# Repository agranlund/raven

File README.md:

# Raven
### A homemade computer based on Motorola MC68060 + DSP56303
This computer is designed to be an Atari compatible clone. It runs clean GEM/TOS applications natively, and very old hardware-banging ST games through an emulation layer.

Some of the more imporant bits in this slightly disorganized repo:
- [Hardware](hw/raven/a2/) - KiCad schematics and PCB. Interactive BOM, revision history.
- [Firmware](fw/) - [CUPL bus logic](fw/a2/), [CKBD keyboard controller](fw/ckbd/)
- [Software](sw/) - [bootloader and monitor](sw/rom/boot/), [TOS bios extension](sw/rvbios/), [ISA PnP bios and drivers](sw/isa/), [graphics drivers](sw/rvnova/), [sound drivers](sw/rvsnd/), [misc utils](sw/tools/)

## Links and resources:
- Youtube: https://www.youtube.com/@granlund23/videos
- Forum: https://www.exxosforum.co.uk/forum/viewforum.php?f=119

## This is not a consumer product.
I have no formal EE training or education. The computer is primarily designed as a one-off for myself, for fun and learning and as a platform that can provide a whole range of interesting areas of programming and/or hardware tinkering.

All hardware and software sources are provided as-is and for free but comes with no guarantees or promise of support.

The computer works for me and can run EmuTOS, FreeMiNT or MagiC but if you decide to build or buy this board I very much recommend coming in with a DIY mindset -- Knowledge and tools to perform hardware-level debugging and/or very low level software debugging is highly recommended.

The forum is also a good place to get help and ask questions regarding bringup or any other topics.

Rev.A1 is slightly easier to build and has seen 10+ other people building working ones.

Rev.A2 is an incremental update where the largest addition is the DSP56303 but it has only been built and tested by myself so far.

## Specifications Rev.A2
- Motorola 68060 CPU @ 96Mhz
- Motorola 56303 DSP @ 90Mhz
- Max 48MB RAM
- Max 16MB ROM
- USB Mouse & Keyboard
- 1Mbps serial port
- Legacy Atari serial port
- Legacy Atari parallel port
- Legacy Atari joystick ports
- IDE Harddisk interface
- Realtime clock
- Midi In/Out
- YM2149 sound
- MC68901 MFP x2
- ISA 16bit expansion slots x4

## Required or recommended parts
- Raven motherboard
	- [Revision.A2](hw/raven/a2/)
    - [Revision.A1](hw/raven/a1/)
    	- [USB upgrade](hw/raven/a1/upgrades/ckbd/)
- RAM modules
    - [16MB 55ns](hw/simm/ram_16M55/)
- ROM module
    - [55ns SMD](hw/simm/rom_SMD/)
    - [55ns PLCC](hw/simm/rom_PLCC/)
- ATX power supply
- USB keyboard and mouse (PS/2 for Rev.A1 without USB upgrade)
- Some kind of suitable 44pin IDE->CF adapter
- RS232<->USB cable capable of 1Mbps
- ISA graphics card.
    - SVGA with hardware acceleration
        - Cirrus GD5434, GD5429, GD5428, GD5426
        - WDC WD90C33, WD90C31
        - Tseng ET4000/W32i
        - ATI Mach32
    - SVGA without hardware acceleration
        - Tseng ET4000AX
        - (untested) Cirrus GD5424, GD5422
        - (untested) WD90C30
    - Cards not listed above have a high chance of working but only in standard VGA resolutions.
- ISA Network card.
	- RTL8019AS based card
- ISA soundcard
	- SoundBlaster compatible
	- Gravis Ultrasound

## Additional tools
- [ROM Simm programmer](hw/simm/programmer/)
- Programmer for ATF1508AS, for example ATDH1150-USB
- Programmer for ATF22V10C, for example XGecu TL866II-Plus
- (Rev.A1 without USB upgrade) Programmer for PIC16F876A, for example XGecu TL866II-Plus

## License

Hardware + CUPL logic are CERN-OHL-2.0. My own software is mostly GPL v2+, 3rd party code keeps its original license. Where a folder differs it'll have its own license file.

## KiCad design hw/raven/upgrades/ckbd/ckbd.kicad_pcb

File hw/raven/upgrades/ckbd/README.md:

# Eiffel upgrade module (rev.d) for Raven.A1

- Plugs into the Eiffel socket instead of the Eiffel PIC.
- Retains support for PS/2 mouse+keyboard, joystick and motherboard temperature sensor.
- Adds USB mouse and keyboard support on an internal USB header.
- Adds support for legacy Atari and Amiga mice (*)
- Adds support for reading CPU temperature (*)
- Adds support for software controlled shutdown (*)

### Firmware:
Binary, sourcecode, and programming instructions can be found here:
* [ckbd firmware](../../../../fw/ckbd/) 

(*) Features marked with an asterix requires soldering patch wires on the motherboard.
All solder points are available on through hole components and can be done on the underside of the motherboard.

#### Support for right mouse button on Legacy mice (not needed for USB or PS2)
- J606:A9  <-> J606:B6 (mouse right button - joystick1 fire button)
#### Support for CPU temperature readout
- U107:M15 <-> U107:M16 (CPU Therm1 - GND)
- U107:L15 <-> U301:26 (CPU Therm0 - Eiffel:Temp2)
#### Support for software controlled shutdown
- SW201:2 <-> U301:25 (PWR switch - Eiffel:PwrOff)

## BOM

| Manufacturer  | Part number       | Value     | Qty | Ref                 | Note |
|---------------|-------------------|-----------|-----|---------------------|------|
| WCH           | CH559L            | CH559L    | 1   | U101                |      |
| Yageo         | RT1206FRE0710KL   | 10K       | 3   | R103,R105,R106      |      |
| Yageo         | RT1206FRE071KL    | 1K        | 4   | R101,R102,R104,R107 |      |
| Kemet         | C1206C105K4RACTU  | 1u        | 2   | C103,C104           |      |
| Kemet         | C1206C104K5RACTU  | 0.1u      | 2   | C102,C105           |      |
| Kemet         | C1206C334K5RACTU  | 0.33u     | 1   | C101                |      |
| ?             | pinheader round   | 1x14      | 2   | J101,J102           | (1)  |
| ?             | pinheader square  | 2x5       | 1   | J103                | (2)  |
| ?             | pinheader square  | 1x4       | 1   | J104                | (2)  |

(1) J101,J102 needs to be round machined pins that can fit in a dip socket.
40-pin breakaway strips can be found here:
https://www.exxosforum.co.uk/atari/store2/#0132

(2) J103,J104 are standard square pin headers which can be found anywhere.
40-pin breakaway strips can be found here:
https://www.exxosforum.co.uk/atari/store2/#0158

## Notes for previous rev.c boards:

The eiffel controlled fan does not work in the previous version of this board.

This can be fixed by soldering a ~1K resistor connecting pins FAN1 and +5V which are both found on the right row of the Eiffel connector.

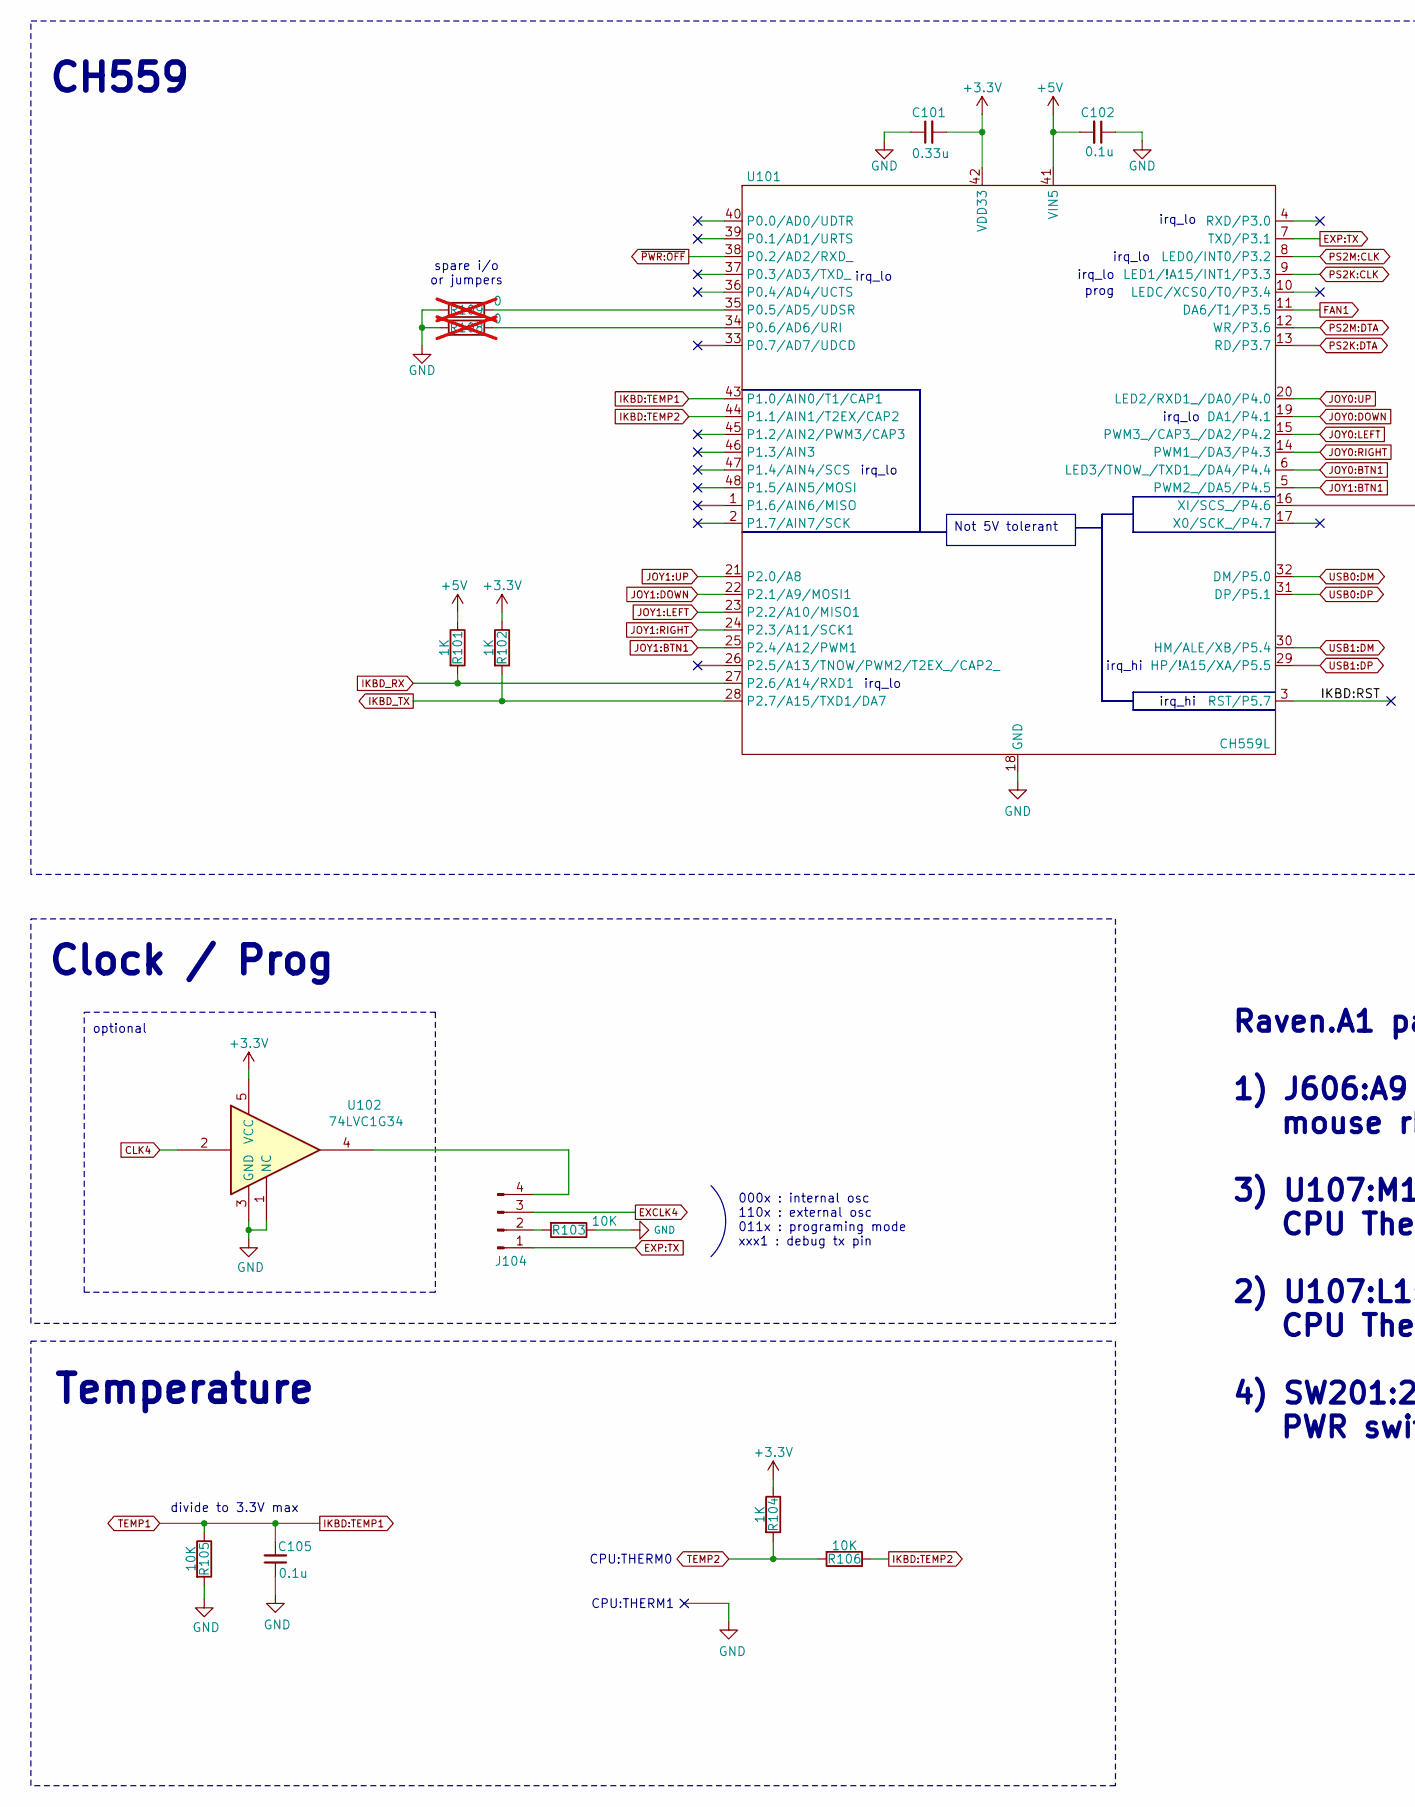
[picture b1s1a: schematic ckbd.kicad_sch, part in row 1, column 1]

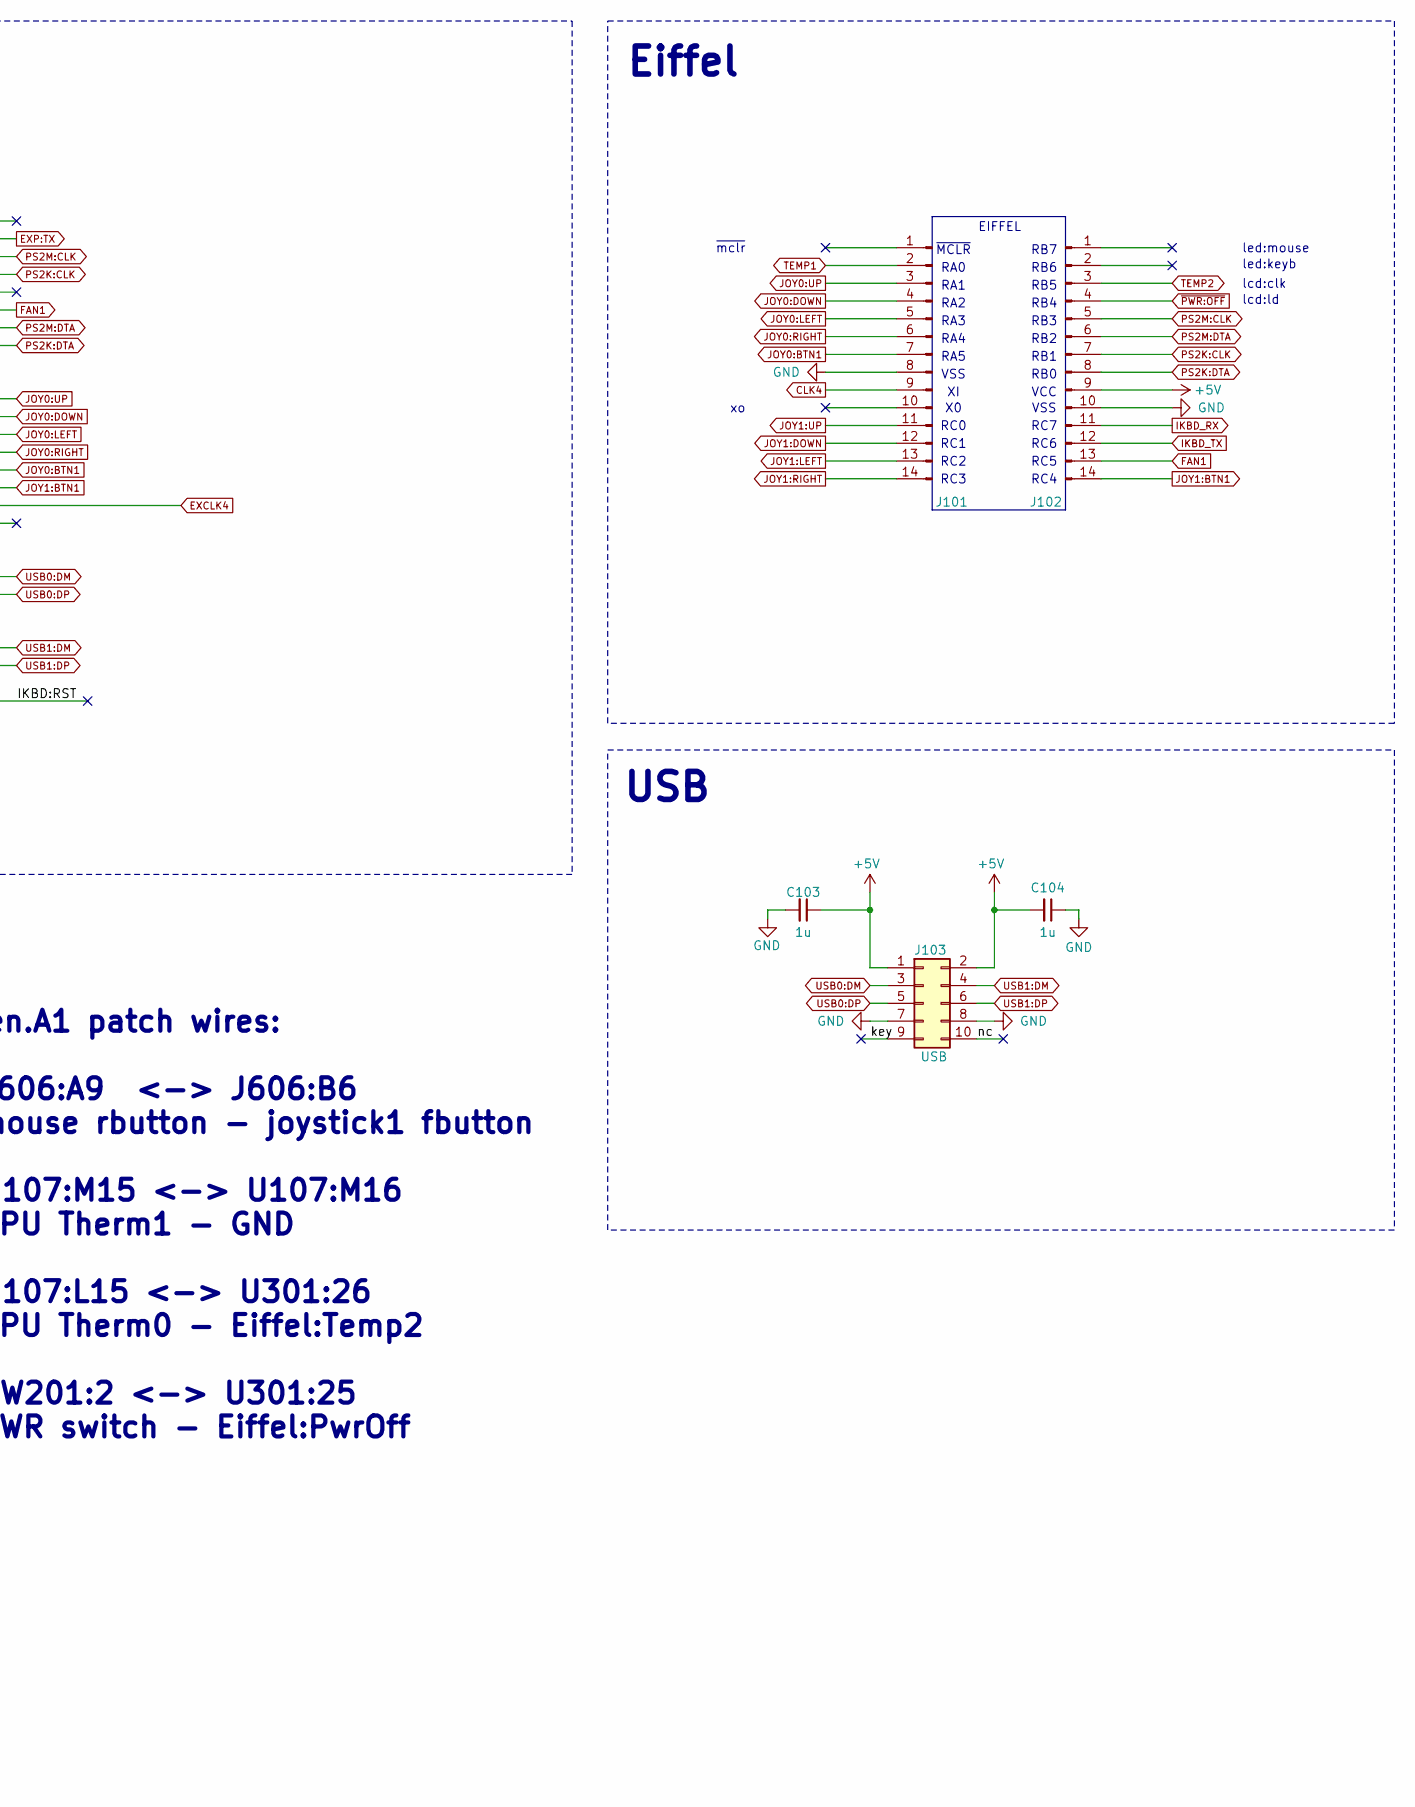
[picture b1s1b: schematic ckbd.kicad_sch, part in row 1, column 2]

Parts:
C101: 0.33u; C_1206_3216Metric_Pad1.33x1.80mm_HandSolder; Manufacturer_Part_Number C1206C334K5RACTU
C102, C105: 0.1u; C_1206_3216Metric_Pad1.33x1.80mm_HandSolder; Manufacturer_Part_Number C1206C104K5RACTU
C103, C104: 1u; C_1206_3216Metric_Pad1.33x1.80mm_HandSolder; Manufacturer_Part_Number C1206C105K4RACTU
J101, J102: PinHeader_1x14_P2.54mm_Vertical
J103: USB; PinHeader_2x05_P2.54mm_Vertical
J104: PinHeader_1x04_P2.54mm_Vertical; Manufacturer_Part_Number 61300411121
R101, R102, R104: 1K; R_1206_3216Metric_Pad1.30x1.75mm_HandSolder; Manufacturer_Part_Number RT1206FRE071KL
R103, R105, R106: 10K; R_1206_3216Metric_Pad1.30x1.75mm_HandSolder; Manufacturer_Part_Number RT1206FRE0710KL
R108, R109: 0; R_1206_3216Metric; not fitted
U101: CH559L; LQFP-48_7x7mm_P0.5mm; Manufacturer_Part_Number CH559L
U102: 74LVC1G34; SOT-23-5_HandSoldering; Manufacturer_Part_Number SN74LVC1G34DBVRG4

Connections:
+3.3V: C101.2, R102.1, R104.1, U101.42 (VDD33), U102.5 (VCC)
+5V: C102.2, C103.1, C104.2, J102.9, J103.1, J103.2, R101.1, U101.41 (VIN5); also elsewhere on the board
/IKBD:RST: U101.3 (RST/P5.7)
/nc: J103.10
CLK4: J101.9, U102.2
EXCLK4: J104.3, U101.16 (XI/SCS_/P4.6)
EXP:TX: J104.1, U101.7 (TXD/P3.1)
FAN1: J102.13, U101.11 (DA6/T1/P3.5); also elsewhere on the board
GND: C101.1, C102.1, C103.2, C104.1, C105.1, J101.8, J102.10, J103.7, J103.8, R103.1, R105.2, R108.1, R109.1, U101.18 (GND), U102.1 (NC), U102.3 (GND)
IKBD:TEMP1: C105.2, J101.2, R105.1, U101.43 (P1.0/AIN0/T1/CAP1)
IKBD:TEMP2: R106.1, U101.44 (P1.1/AIN1/T2EX/CAP2)
IKBD_RX: J102.11, R101.2, U101.27 (P2.6/A14/RXD1)
IKBD_TX: J102.12, R102.2, U101.28 (P2.7/A15/TXD1/DA7)
JOY0:BTN1: J101.7, U101.6 (LED3/TNOW_/TXD1_/DA4/P4.4)
JOY0:DOWN: J101.4, U101.19 (DA1/P4.1)
JOY0:LEFT: J101.5, U101.15 (PWM3_/CAP3_/DA2/P4.2)
JOY0:RIGHT: J101.6, U101.14 (PWM1_/DA3/P4.3)
JOY0:UP: J101.3, U101.20 (LED2/RXD1_/DA0/P4.0)
JOY1:BTN1: J102.14, U101.5 (PWM2_/DA5/P4.5), U101.25 (P2.4/A12/PWM1)
JOY1:DOWN: J101.12, U101.22 (P2.1/A9/MOSI1)
JOY1:LEFT: J101.13, U101.23 (P2.2/A10/MISO1)
JOY1:RIGHT: J101.14, U101.24 (P2.3/A11/SCK1)
JOY1:UP: J101.11, U101.21 (P2.0/A8)
unnamed: J104.2, R103.2
unnamed: J104.4, U102.4
unnamed: R109.2, U101.35 (P0.5/AD5/UDSR)
unnamed: R108.2, U101.34 (P0.6/AD6/URI)
PS2K:CLK: J102.7, U101.9 (LED1/!A15/INT1/P3.3)
PS2K:DTA: J102.8, U101.13 (RD/P3.7)
PS2M:CLK: J102.5, U101.8 (LED0/INT0/P3.2)
PS2M:DTA: J102.6, U101.12 (WR/P3.6)
TEMP2: J102.3, R104.2, R106.2
USB0:DM: J103.3, U101.32 (DM/P5.0)
USB0:DP: J103.5, U101.31 (DP/P5.1)
USB1:DM: J103.4, U101.30 (HM/ALE/XB/P5.4)
USB1:DP: J103.6, U101.29 (HP/!A15/XA/P5.5)
~PWR:OFF: J102.4, U101.38 (P0.2/AD2/RXD_)

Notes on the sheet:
RC7
EIFFEL
RB6
RC4
irq_lo
RA4
RA0
VCC
RB2
RB5
RB7
RC0
RB1
Eiffel
irq_hi
~{MCLR}
led:keyb
lcd:clk
CH559
USB
RB4
lcd:ld
RC3
000x : internal osc 110x : external osc 011x : programing mode xxx1 : debug tx pin
CPU:THERM1
divide to 3.3V max
RB0
RC6
Temperature
CPU:THERM0
RA3
RA2
prog
VSS
led:mouse
RB3
RC2
Clock / Prog
RA5
RA1

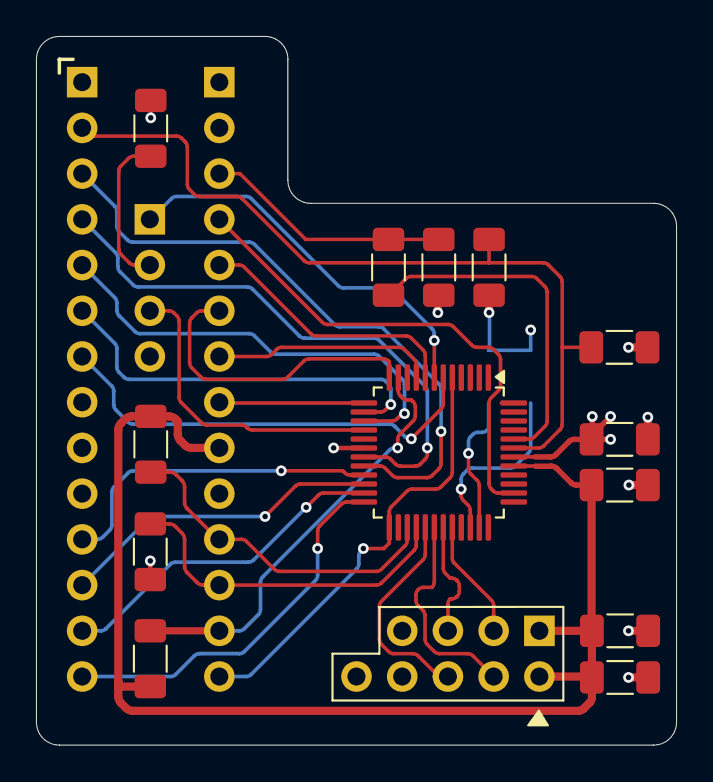
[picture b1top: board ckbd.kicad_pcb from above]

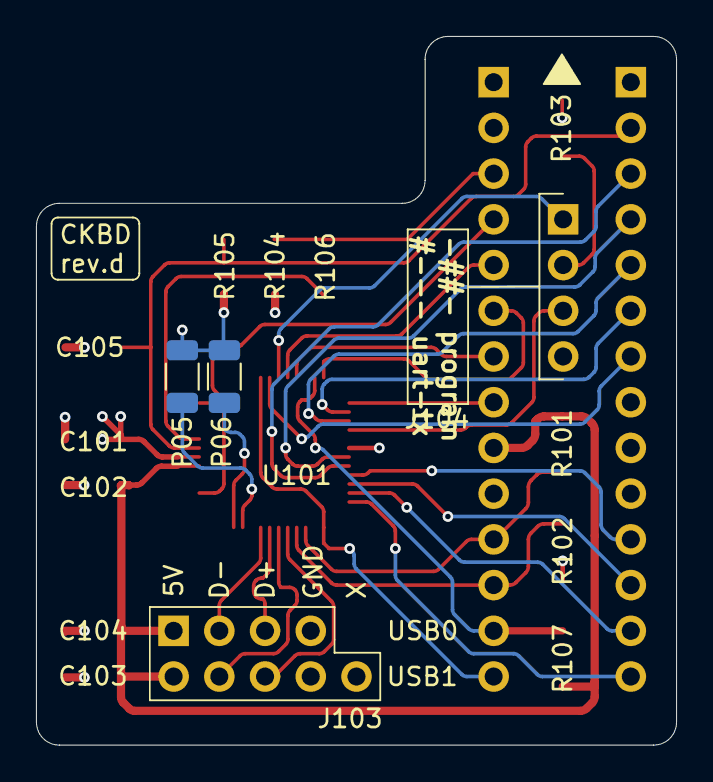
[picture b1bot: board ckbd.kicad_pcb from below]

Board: 4 copper layers, 35.6 x 39.4 mm, 19 parts (2 on the bottom side), 33 nets.

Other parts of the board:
R107: 1K; R_1206_3216Metric_Pad1.30x1.75mm_HandSolder

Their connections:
+5V: R107.1; also elsewhere on the board
FAN1: R107.2; also elsewhere on the board

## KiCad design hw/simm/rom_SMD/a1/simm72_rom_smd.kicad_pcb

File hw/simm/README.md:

# Info:
- Simm modules should be manufactured with a thickness of 1.2 mm
- They are probably be a tiny bit too wide but do fit in the socket ok. Would be good to shave off a millimeter or so in a future update.
- Unless stated otherwise these hardware designs are licensed under CERN-OHL-P v2
    - See LICENSE.md or visit https://cern.ch/cern-ohl

### Sub projects:
- breakout
	- simple simm breakout module for debugging. untested.
- panel
	- template for merging two simms onto one board separated by mouse-bites
- programmer
	- Pico based programmer for ROM simm modules
- ram_16M55
	- 16MB 55ns RAM module
- ram_8M10
	- 8MB 10ns RAM module
- rom_16M55
	- module with SMD roms (recommended)
- rom_2M55
	- module for 4x socketed PLCC roms
- template
	- blank simm module template

### Pinout:

1. vcc     * 
2. a2
3. a3
4. a4
5. a5
6. a6
7. a7
8. a8
9. a9
10. gnd     *
11. d31
12. d30
13. d29
14. d28
15. d27
16. d26
17. d25
18. d24
19. gnd     *
20. d23
21. d22
22. d21
23. d20
24. d19
25. d18
26. d17
27. d16
28. gnd     *
29. d15
30. d14
31. d13
32. d12
33. d11
34. d10
35. d9
36. d8
37. gnd     *
38. d7
39. d6
40. d5
41. d4
42. d3
43. d2
44. d1
45. d0
46. gnd     *
47. a21
48. a20
49. a19
50. a18
51. a17
52. a16
53. gnd     *
54. a15
55. a14
56. a13
57. a12
58. a11
59. a10
60. a9
61. a8
62. gnd     *
63. b0
64. b1
65. b2
66. b3
67. nc      -
68. oe
69. we
70. nc      -
71. nc      -
72. vcc     *

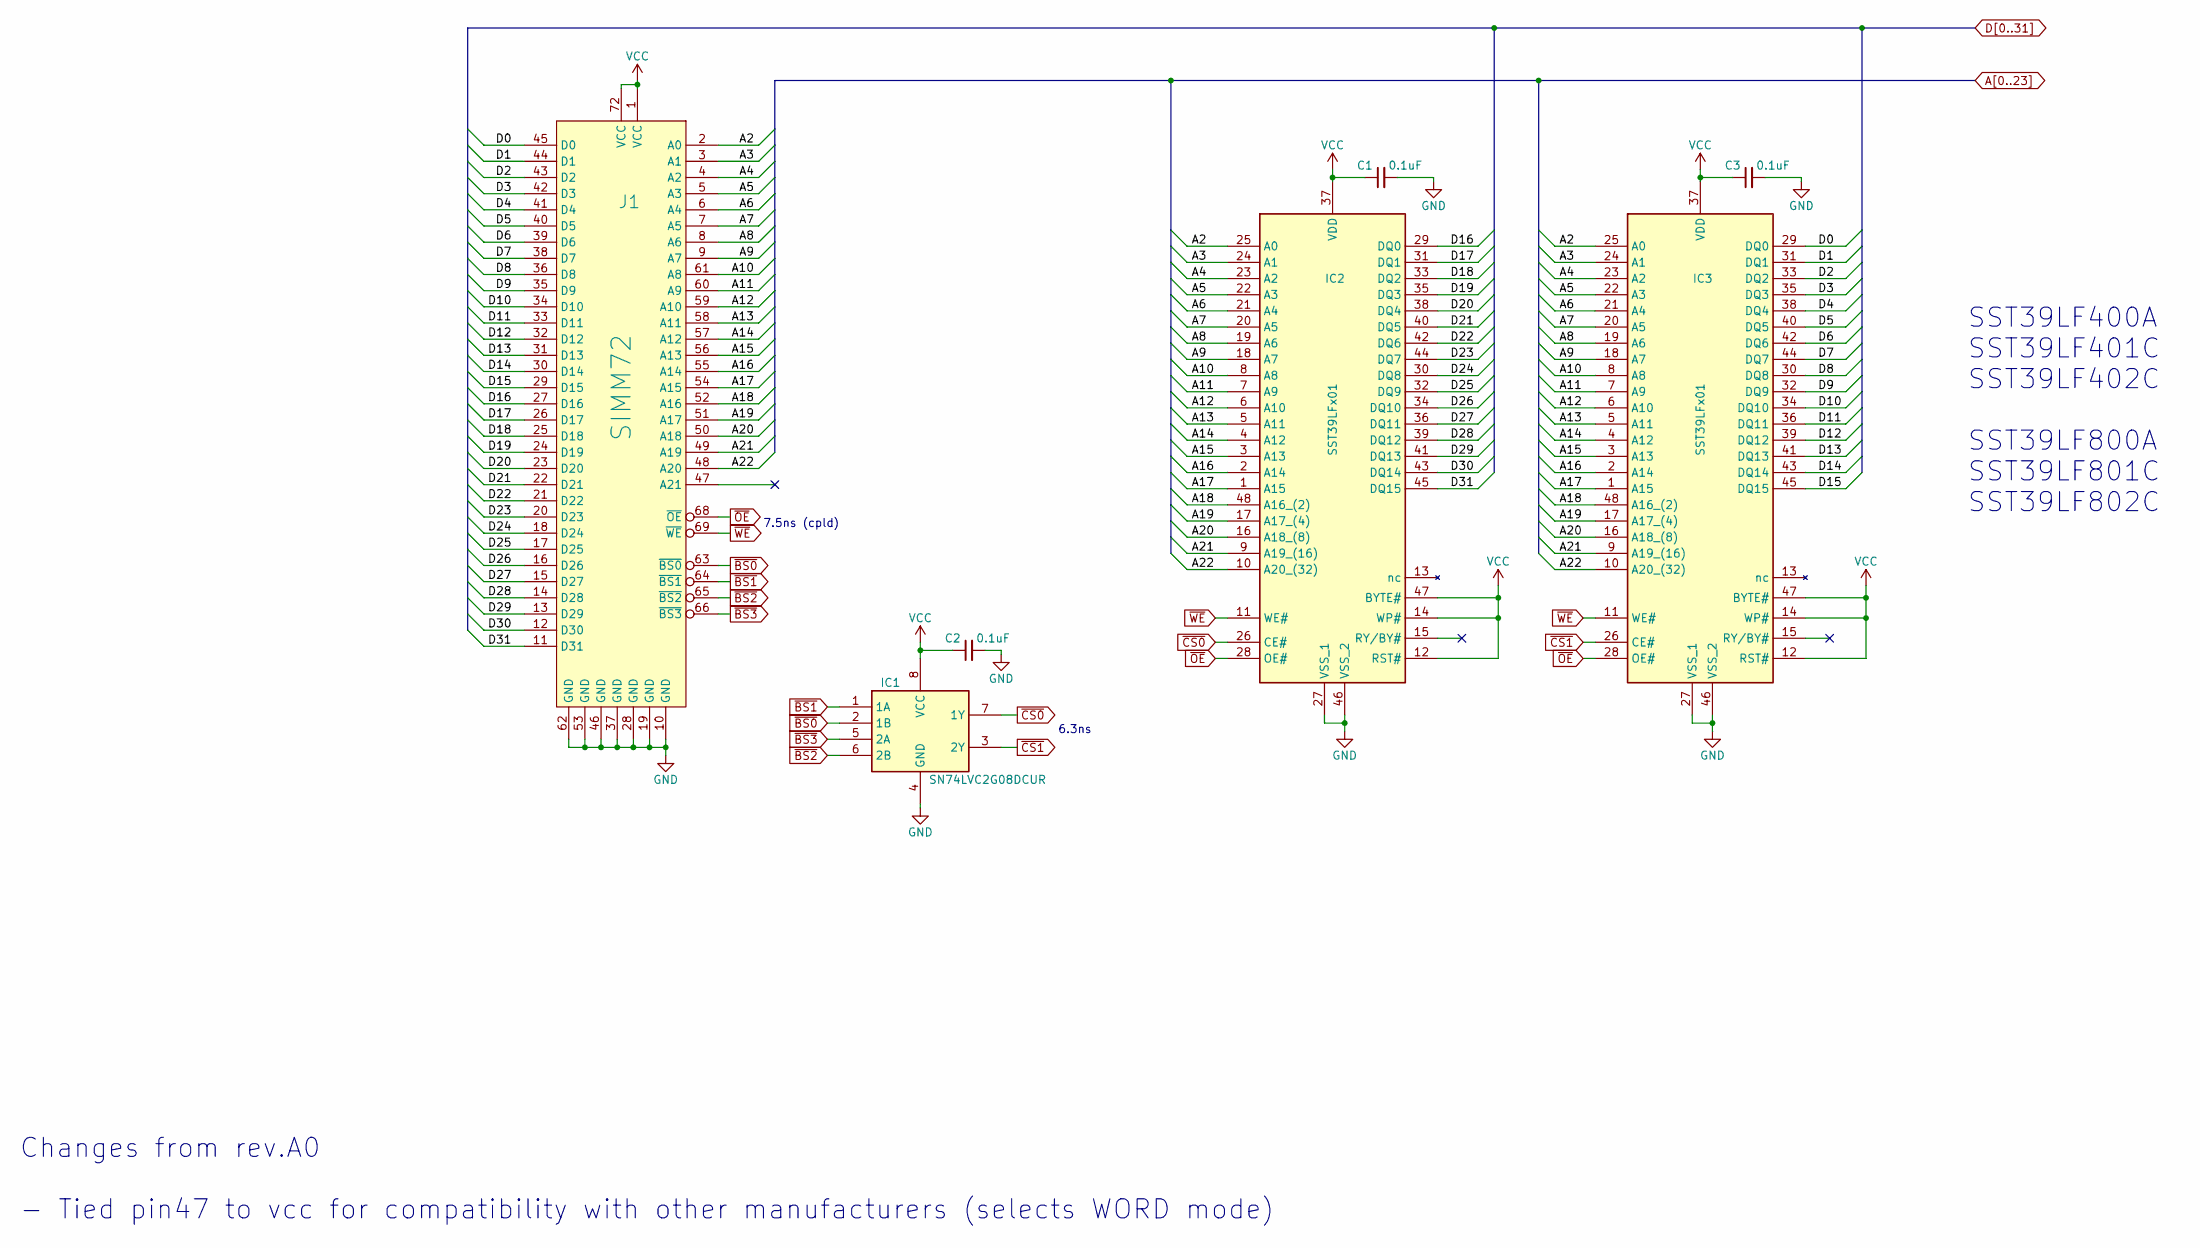
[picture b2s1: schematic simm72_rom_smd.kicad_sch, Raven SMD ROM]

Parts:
C1, C2, C3: 0.1uF; C_1206_3216Metric_Pad1.33x1.80mm_HandSolder; Manufacturer_Part_Number C1206C104K5RACTU
IC1: SN74LVC2G08DCUR; SOP50P310X90-8N; Mouser Part Number 595-SN74LVC2G08DCUR
IC2, IC3: SST39LFx01; SOP50P2000X120-48N; Mouser Part Number 579-39LF401C554CEKET
J1: SIMM72; SIMM72_edge

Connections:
A2: IC2.25 (A0), IC3.25 (A0), J1.2 (A0)
A3: IC2.24 (A1), IC3.24 (A1), J1.3 (A1)
A4: IC2.23 (A2), IC3.23 (A2), J1.4 (A2)
A5: IC2.22 (A3), IC3.22 (A3), J1.5 (A3)
A6: IC2.21 (A4), IC3.21 (A4), J1.6 (A4)
A7: IC2.20 (A5), IC3.20 (A5), J1.7 (A5)
A8: IC2.19 (A6), IC3.19 (A6), J1.8 (A6)
A9: IC2.18 (A7), IC3.18 (A7), J1.9 (A7)
A10: IC2.8 (A8), IC3.8 (A8), J1.61 (A8)
A11: IC2.7 (A9), IC3.7 (A9), J1.60 (A9)
A12: IC2.6 (A10), IC3.6 (A10), J1.59 (A10)
A13: IC2.5 (A11), IC3.5 (A11), J1.58 (A11)
A14: IC2.4 (A12), IC3.4 (A12), J1.57 (A12)
A15: IC2.3 (A13), IC3.3 (A13), J1.56 (A13)
A16: IC2.2 (A14), IC3.2 (A14), J1.55 (A14)
A17: IC2.1 (A15), IC3.1 (A15), J1.54 (A15)
A18: IC2.48 (A16_(2)), IC3.48 (A16_(2)), J1.52 (A16)
A19: IC2.17 (A17_(4)), IC3.17 (A17_(4)), J1.51 (A17)
A20: IC2.16 (A18_(8)), IC3.16 (A18_(8)), J1.50 (A18)
A21: IC2.9 (A19_(16)), IC3.9 (A19_(16)), J1.49 (A19)
A22: IC2.10 (A20_(32)), IC3.10 (A20_(32)), J1.48 (A20)
D0: IC3.29 (DQ0), J1.45 (D0)
D1: IC3.31 (DQ1), J1.44 (D1)
D2: IC3.33 (DQ2), J1.43 (D2)
D3: IC3.35 (DQ3), J1.42 (D3)
D4: IC3.38 (DQ4), J1.41 (D4)
D5: IC3.40 (DQ5), J1.40 (D5)
D6: IC3.42 (DQ6), J1.39 (D6)
D7: IC3.44 (DQ7), J1.38 (D7)
D8: IC3.30 (DQ8), J1.36 (D8)
D9: IC3.32 (DQ9), J1.35 (D9)
D10: IC3.34 (DQ10), J1.34 (D10)
D11: IC3.36 (DQ11), J1.33 (D11)
D12: IC3.39 (DQ12), J1.32 (D12)
D13: IC3.41 (DQ13), J1.31 (D13)
D14: IC3.43 (DQ14), J1.30 (D14)
D15: IC3.45 (DQ15), J1.29 (D15)
D16: IC2.29 (DQ0), J1.27 (D16)
D17: IC2.31 (DQ1), J1.26 (D17)
D18: IC2.33 (DQ2), J1.25 (D18)
D19: IC2.35 (DQ3), J1.24 (D19)
D20: IC2.38 (DQ4), J1.23 (D20)
D21: IC2.40 (DQ5), J1.22 (D21)
D22: IC2.42 (DQ6), J1.21 (D22)
D23: IC2.44 (DQ7), J1.20 (D23)
D24: IC2.30 (DQ8), J1.18 (D24)
D25: IC2.32 (DQ9), J1.17 (D25)
D26: IC2.34 (DQ10), J1.16 (D26)
D27: IC2.36 (DQ11), J1.15 (D27)
D28: IC2.39 (DQ12), J1.14 (D28)
D29: IC2.41 (DQ13), J1.13 (D29)
D30: IC2.43 (DQ14), J1.12 (D30)
D31: IC2.45 (DQ15), J1.11 (D31)
GND: C1.2, C2.2, C3.2, IC1.4 (GND), IC2.27 (VSS_1), IC2.46 (VSS_2), IC3.27 (VSS_1), IC3.46 (VSS_2), J1.10 (GND), J1.19 (GND), J1.28 (GND), J1.37 (GND), J1.46 (GND), J1.53 (GND), J1.62 (GND)
VCC: C1.1, C2.1, C3.1, IC1.8 (VCC), IC2.12 (RST#), IC2.14 (WP#), IC2.37 (VDD), IC2.47 (BYTE#), IC3.12 (RST#), IC3.14 (WP#), IC3.37 (VDD), IC3.47 (BYTE#), J1.1 (VCC), J1.72 (VCC)
~BS0: IC1.2 (1B), J1.63 (~BS0)
~BS1: IC1.1 (1A), J1.64 (~BS1)
~BS2: IC1.6 (2B), J1.65 (~BS2)
~BS3: IC1.5 (2A), J1.66 (~BS3)
~CS0: IC1.7 (1Y), IC2.26 (CE#)
~CS1: IC1.3 (2Y), IC3.26 (CE#)
~OE: IC2.28 (OE#), IC3.28 (OE#), J1.68 (~OE)
~WE: IC2.11 (WE#), IC3.11 (WE#), J1.69 (~WE)

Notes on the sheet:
7.5ns (cpld)
6.3ns
Changes from rev.A0 - Tied pin47 to vcc for compatibility with other manufacturers (selects WORD mode)
SST39LF400A SST39LF401C SST39LF402C SST39LF800A SST39LF801C SST39LF802C

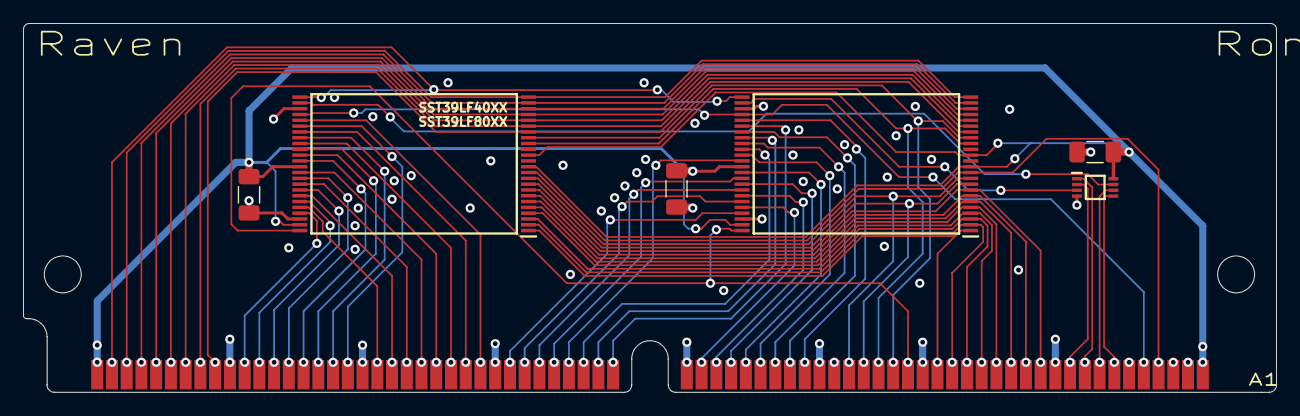
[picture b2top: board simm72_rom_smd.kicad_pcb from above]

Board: 4 copper layers, 108.0 x 31.8 mm, 7 parts (0 on the bottom side), 63 nets.

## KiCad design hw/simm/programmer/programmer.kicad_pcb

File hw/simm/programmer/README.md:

# Raven ROM programmer

## BOM

| Manufacturer          | Part number                 | Value       | Count | Ref                                   |
|-----------------------|-----------------------------|-------------|-------|---------------------------------------|
| Vishay                | K104K10X7RF53H5             | 0.1u        | 3     | C101, C102, C103                      |
| Texas Instruments     | SN74HC273N                  | 74HC273     | 3     | U101, U103, U104                      |
| Bourns                | 4609X-101-102LF             | 8x1K        | 1     | RN101                                 |
| Alps Alpine           | SKHHARA010                  | button      | 1     | SW101                                 |
| TE Connectivity       | 5822030-3                   | simm        | 1     | J101                                  |
| Raspberry Pi          | SC0915                      | Pi Pico     | 1     | U102                                  |

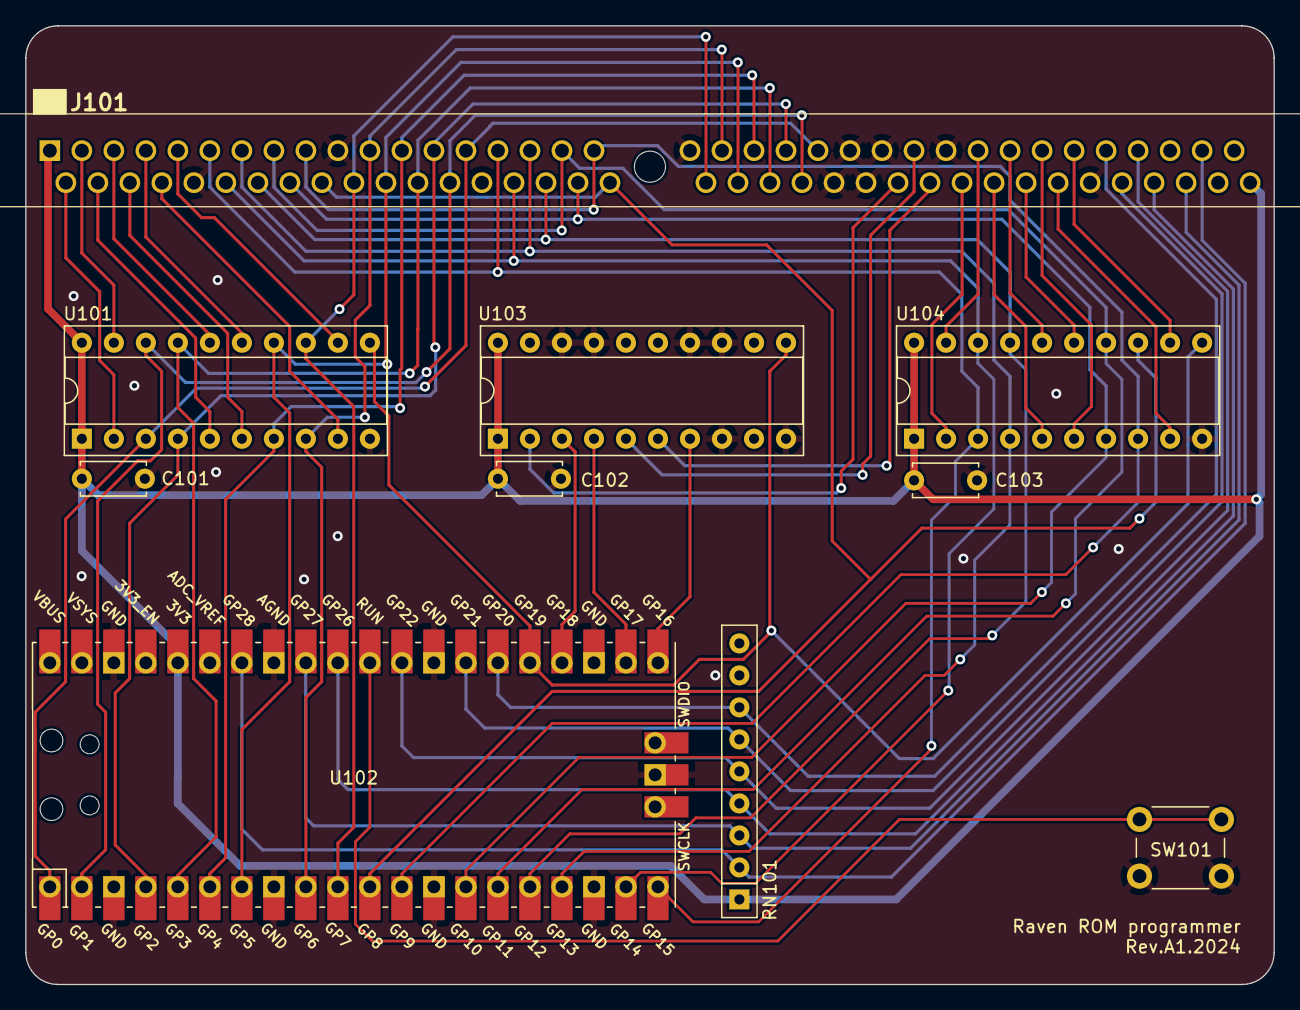
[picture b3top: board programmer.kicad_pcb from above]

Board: 2 copper layers, 99.1 x 76.1 mm, 10 parts (0 on the bottom side), 48 nets.

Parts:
C101, C102, C103: 0.1uF; C_Disc_D5.0mm_W2.5mm_P5.00mm
J101: SIMM72; SIMM72_v_lpol
RN101: 8x10K; R_Array_SIP9
SW101: SW_Push_PCB_THT; SW_PUSH_6mm_H4.3mm
U101, U103, U104: 74HC273; DIP-20_W7.62mm_Socket
U102: RPico

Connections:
+3.3V: C101.1, C102.1, C103.1, J101.1 (VCC), J101.72 (VCC), RN101.1 (common), U101.1 (~Mr), U101.20 (VCC), U102.36 (3V3), U103.1 (~Mr), U103.20 (VCC), U104.1 (~Mr), U104.20 (VCC)
A0: J101.2 (A0), U101.2 (Q0)
A1: J101.3 (A1), U101.19 (Q7)
A2: J101.4 (A2), U101.5 (Q1)
A3: J101.5 (A3), U101.16 (Q6)
A4: J101.6 (A4), U101.6 (Q2)
A5: J101.7 (A5), U101.15 (Q5)
A6: J101.8 (A6), U101.9 (Q3)
A7: J101.9 (A7), U101.12 (Q4)
A8: J101.61 (A8), U104.12 (Q4)
A9: J101.60 (A9), U104.9 (Q3)
A10: J101.59 (A10), U104.6 (Q2)
A11: J101.58 (A11), U104.15 (Q5)
A12: J101.57 (A12), U104.16 (Q6)
A13: J101.56 (A13), U104.5 (Q1)
A14: J101.55 (A14), U104.19 (Q7)
A15: J101.54 (A15), U104.2 (Q0)
A16: J101.52 (A16), U103.6 (Q2)
A17: J101.51 (A17), U103.5 (Q1)
A18: J101.50 (A18), U103.2 (Q0)
AD0: J101.27 (D16), J101.45 (D0), U101.3 (D0), U102.1 (GPIO0)
AD1: J101.26 (D17), J101.44 (D1), U101.18 (D7), U102.2 (GPIO1)
AD2: J101.25 (D18), J101.43 (D2), U101.4 (D1), U102.4 (GPIO2)
AD3: J101.24 (D19), J101.42 (D3), U101.17 (D6), U102.5 (GPIO3)
AD4: J101.23 (D20), J101.41 (D4), U101.7 (D2), U102.6 (GPIO4)
AD5: J101.22 (D21), J101.40 (D5), U101.14 (D5), U102.7 (GPIO5)
AD6: J101.21 (D22), J101.39 (D6), U101.8 (D3), U102.9 (GPIO6)
AD7: J101.20 (D23), J101.38 (D7), U101.13 (D4), U102.10 (GPIO7)
AD8: J101.18 (D24), J101.36 (D8), U102.11 (GPIO8), U104.13 (D4)
AD9: J101.17 (D25), J101.35 (D9), U102.12 (GPIO9), U104.8 (D3)
AD10: J101.16 (D26), J101.34 (D10), U102.14 (GPIO10), U104.7 (D2)
AD11: J101.15 (D27), J101.33 (D11), U102.15 (GPIO11), U104.14 (D5)
AD12: J101.14 (D28), J101.32 (D12), U102.16 (GPIO12), U104.17 (D6)
AD13: J101.13 (D29), J101.31 (D13), U102.17 (GPIO13), U104.4 (D1)
AD14: J101.12 (D30), J101.30 (D14), U102.19 (GPIO14), U104.18 (D7)
AD15: J101.11 (D31), J101.29 (D15), U102.20 (GPIO15), U104.3 (D0)
AD16: U102.21 (GPIO16), U103.7 (D2)
AD17: U102.22 (GPIO17), U103.4 (D1)
AD18: U102.24 (GPIO18), U103.3 (D0)
ALE: U101.11 (Cp), U102.25 (GPIO19), U103.11 (Cp), U104.11 (Cp)
GND: C101.2, C102.2, C103.2, J101.10 (GND), J101.19 (GND), J101.28 (GND), J101.37 (GND), J101.46 (GND), J101.47 (A21), J101.48 (A20), J101.49 (A19), J101.53 (GND), J101.62 (GND), SW101.2, U101.10 (GND), U102.3 (GND), U102.8 (GND), U102.13 (GND), U102.18 (GND), U102.23 (GND), U102.28 (GND), U102.33 (AGND), U102.38 (GND), U102.42 (GND), U103.8 (D3), U103.10 (GND), U103.13 (D4), U103.14 (D5), U103.17 (D6), U103.18 (D7), U104.10 (GND)
unnamed: SW101.1, U102.30 (RUN)
~DBS0: J101.63 (~BS0), RN101.7 (R6), U102.26 (GPIO20)
~DBS1: J101.64 (~BS1), RN101.6 (R5), U102.27 (GPIO21)
~DBS2: J101.65 (~BS2), RN101.5 (R4), U102.29 (GPIO22)
~DBS3: J101.66 (~BS3), RN101.4 (R3), U102.31 (GPIO26_ADC0)
~DRD: J101.68 (~OE), RN101.3 (R2), U102.32 (GPIO27_ADC1)
~DWR: J101.69 (~WE), RN101.2 (R1), U102.34 (GPIO28_ADC2)

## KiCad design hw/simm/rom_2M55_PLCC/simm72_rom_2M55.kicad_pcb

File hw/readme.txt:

All pcbs are made within JLCPCB tolerances and any Gerbers found here are exported for JLCPCB specifications.

Disclaimer: I am not an electrical engineer.
If anything in here seems stupidly designed, then it probably is.

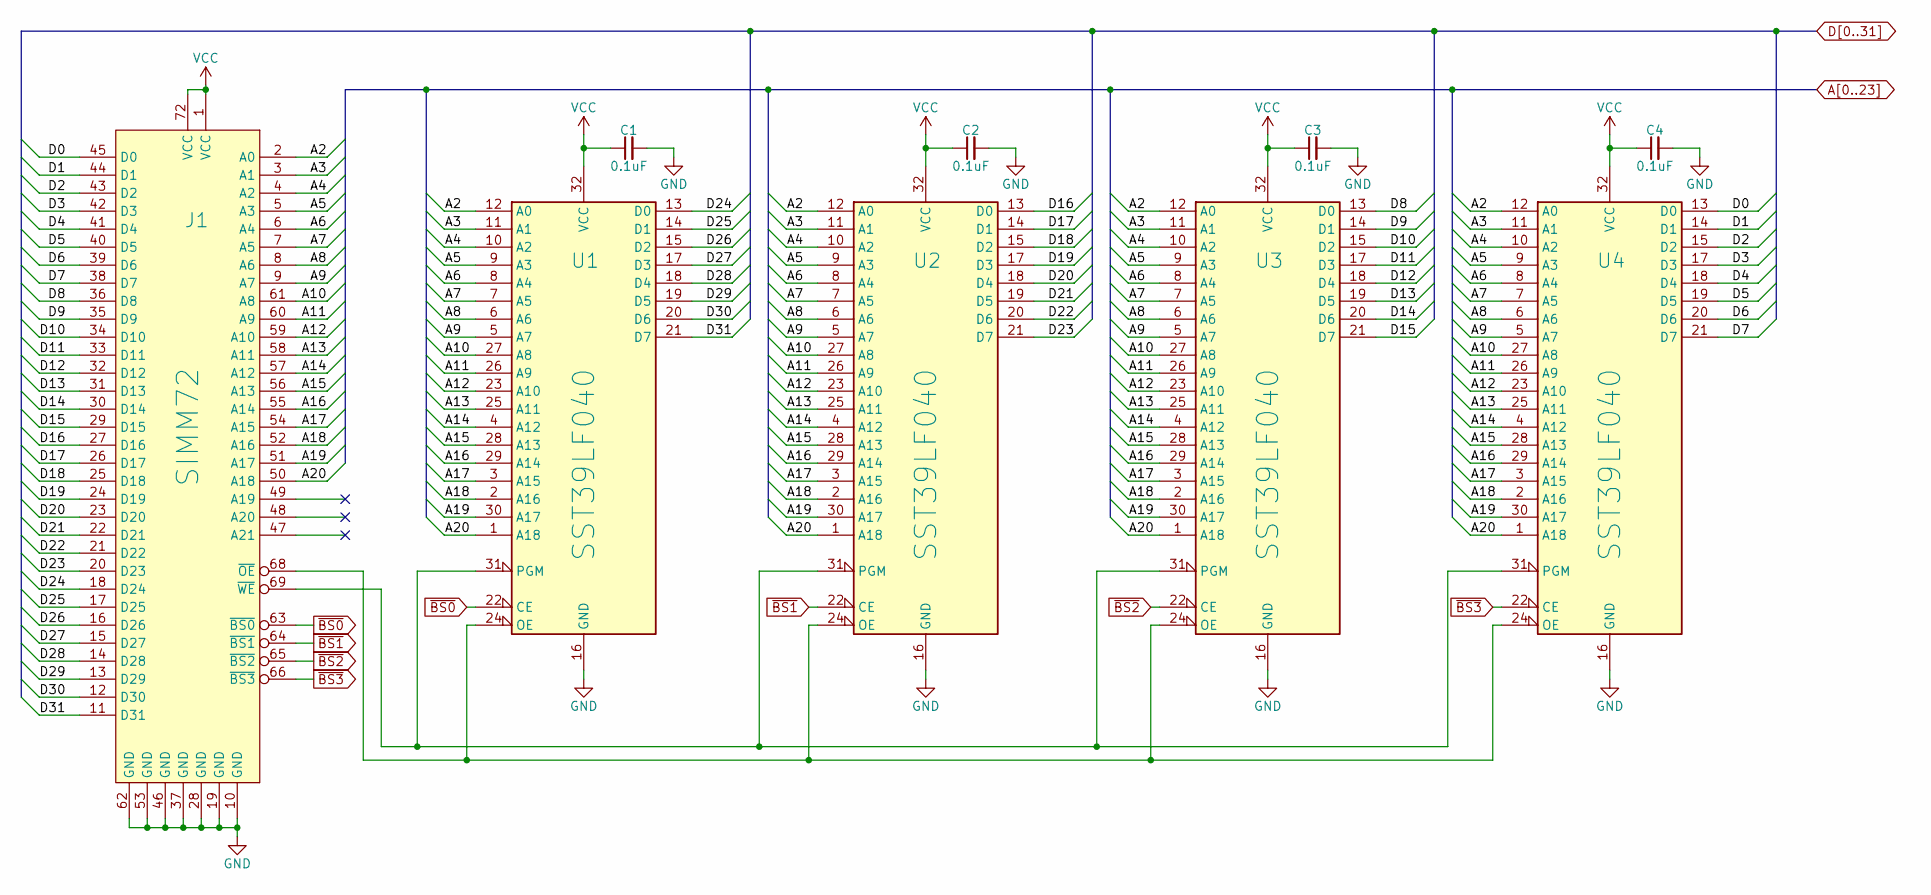
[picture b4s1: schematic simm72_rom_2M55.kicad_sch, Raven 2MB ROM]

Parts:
C1, C2, C3, C4: 0.1uF; C_1206_3216Metric_Pad1.33x1.80mm_HandSolder; Manufacturer_Part_Number C1206C104K5RACTU
J1: SIMM72; SIMM72_edge
U1, U2, U3, U4: SST39LF040; PLCC-32_THT-Socket; Manufacturer_Part_Number SST39LF040-55-4C-NHE-T

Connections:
A2: J1.2 (A0), U1.12 (A0), U2.12 (A0), U3.12 (A0), U4.12 (A0)
A3: J1.3 (A1), U1.11 (A1), U2.11 (A1), U3.11 (A1), U4.11 (A1)
A4: J1.4 (A2), U1.10 (A2), U2.10 (A2), U3.10 (A2), U4.10 (A2)
A5: J1.5 (A3), U1.9 (A3), U2.9 (A3), U3.9 (A3), U4.9 (A3)
A6: J1.6 (A4), U1.8 (A4), U2.8 (A4), U3.8 (A4), U4.8 (A4)
A7: J1.7 (A5), U1.7 (A5), U2.7 (A5), U3.7 (A5), U4.7 (A5)
A8: J1.8 (A6), U1.6 (A6), U2.6 (A6), U3.6 (A6), U4.6 (A6)
A9: J1.9 (A7), U1.5 (A7), U2.5 (A7), U3.5 (A7), U4.5 (A7)
A10: J1.61 (A8), U1.27 (A8), U2.27 (A8), U3.27 (A8), U4.27 (A8)
A11: J1.60 (A9), U1.26 (A9), U2.26 (A9), U3.26 (A9), U4.26 (A9)
A12: J1.59 (A10), U1.23 (A10), U2.23 (A10), U3.23 (A10), U4.23 (A10)
A13: J1.58 (A11), U1.25 (A11), U2.25 (A11), U3.25 (A11), U4.25 (A11)
A14: J1.57 (A12), U1.4 (A12), U2.4 (A12), U3.4 (A12), U4.4 (A12)
A15: J1.56 (A13), U1.28 (A13), U2.28 (A13), U3.28 (A13), U4.28 (A13)
A16: J1.55 (A14), U1.29 (A14), U2.29 (A14), U3.29 (A14), U4.29 (A14)
A17: J1.54 (A15), U1.3 (A15), U2.3 (A15), U3.3 (A15), U4.3 (A15)
A18: J1.52 (A16), U1.2 (A16), U2.2 (A16), U3.2 (A16), U4.2 (A16)
A19: J1.51 (A17), U1.30 (A17), U2.30 (A17), U3.30 (A17), U4.30 (A17)
A20: J1.50 (A18), U1.1 (A18), U2.1 (A18), U3.1 (A18), U4.1 (A18)
D0: J1.45 (D0), U4.13 (D0)
D1: J1.44 (D1), U4.14 (D1)
D2: J1.43 (D2), U4.15 (D2)
D3: J1.42 (D3), U4.17 (D3)
D4: J1.41 (D4), U4.18 (D4)
D5: J1.40 (D5), U4.19 (D5)
D6: J1.39 (D6), U4.20 (D6)
D7: J1.38 (D7), U4.21 (D7)
D8: J1.36 (D8), U3.13 (D0)
D9: J1.35 (D9), U3.14 (D1)
D10: J1.34 (D10), U3.15 (D2)
D11: J1.33 (D11), U3.17 (D3)
D12: J1.32 (D12), U3.18 (D4)
D13: J1.31 (D13), U3.19 (D5)
D14: J1.30 (D14), U3.20 (D6)
D15: J1.29 (D15), U3.21 (D7)
D16: J1.27 (D16), U2.13 (D0)
D17: J1.26 (D17), U2.14 (D1)
D18: J1.25 (D18), U2.15 (D2)
D19: J1.24 (D19), U2.17 (D3)
D20: J1.23 (D20), U2.18 (D4)
D21: J1.22 (D21), U2.19 (D5)
D22: J1.21 (D22), U2.20 (D6)
D23: J1.20 (D23), U2.21 (D7)
D24: J1.18 (D24), U1.13 (D0)
D25: J1.17 (D25), U1.14 (D1)
D26: J1.16 (D26), U1.15 (D2)
D27: J1.15 (D27), U1.17 (D3)
D28: J1.14 (D28), U1.18 (D4)
D29: J1.13 (D29), U1.19 (D5)
D30: J1.12 (D30), U1.20 (D6)
D31: J1.11 (D31), U1.21 (D7)
GND: C1.2, C2.2, C3.2, C4.2, J1.10 (GND), J1.19 (GND), J1.28 (GND), J1.37 (GND), J1.46 (GND), J1.53 (GND), J1.62 (GND), U1.16 (GND), U2.16 (GND), U3.16 (GND), U4.16 (GND)
unnamed: J1.68 (~OE), U1.24 (OE), U2.24 (OE), U3.24 (OE), U4.24 (OE)
unnamed: J1.69 (~WE), U1.31 (PGM), U2.31 (PGM), U3.31 (PGM), U4.31 (PGM)
VCC: C1.1, C2.1, C3.1, C4.1, J1.1 (VCC), J1.72 (VCC), U1.32 (VCC), U2.32 (VCC), U3.32 (VCC), U4.32 (VCC)
~BS0: J1.63 (~BS0), U1.22 (CE)
~BS1: J1.64 (~BS1), U2.22 (CE)
~BS2: J1.65 (~BS2), U3.22 (CE)
~BS3: J1.66 (~BS3), U4.22 (CE)

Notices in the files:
hw/raven/upgrades/ckbd/ckbd.kicad_pcb:
Licensed under CERN-OHL-W v2
(c)2025 Anders Granlund
